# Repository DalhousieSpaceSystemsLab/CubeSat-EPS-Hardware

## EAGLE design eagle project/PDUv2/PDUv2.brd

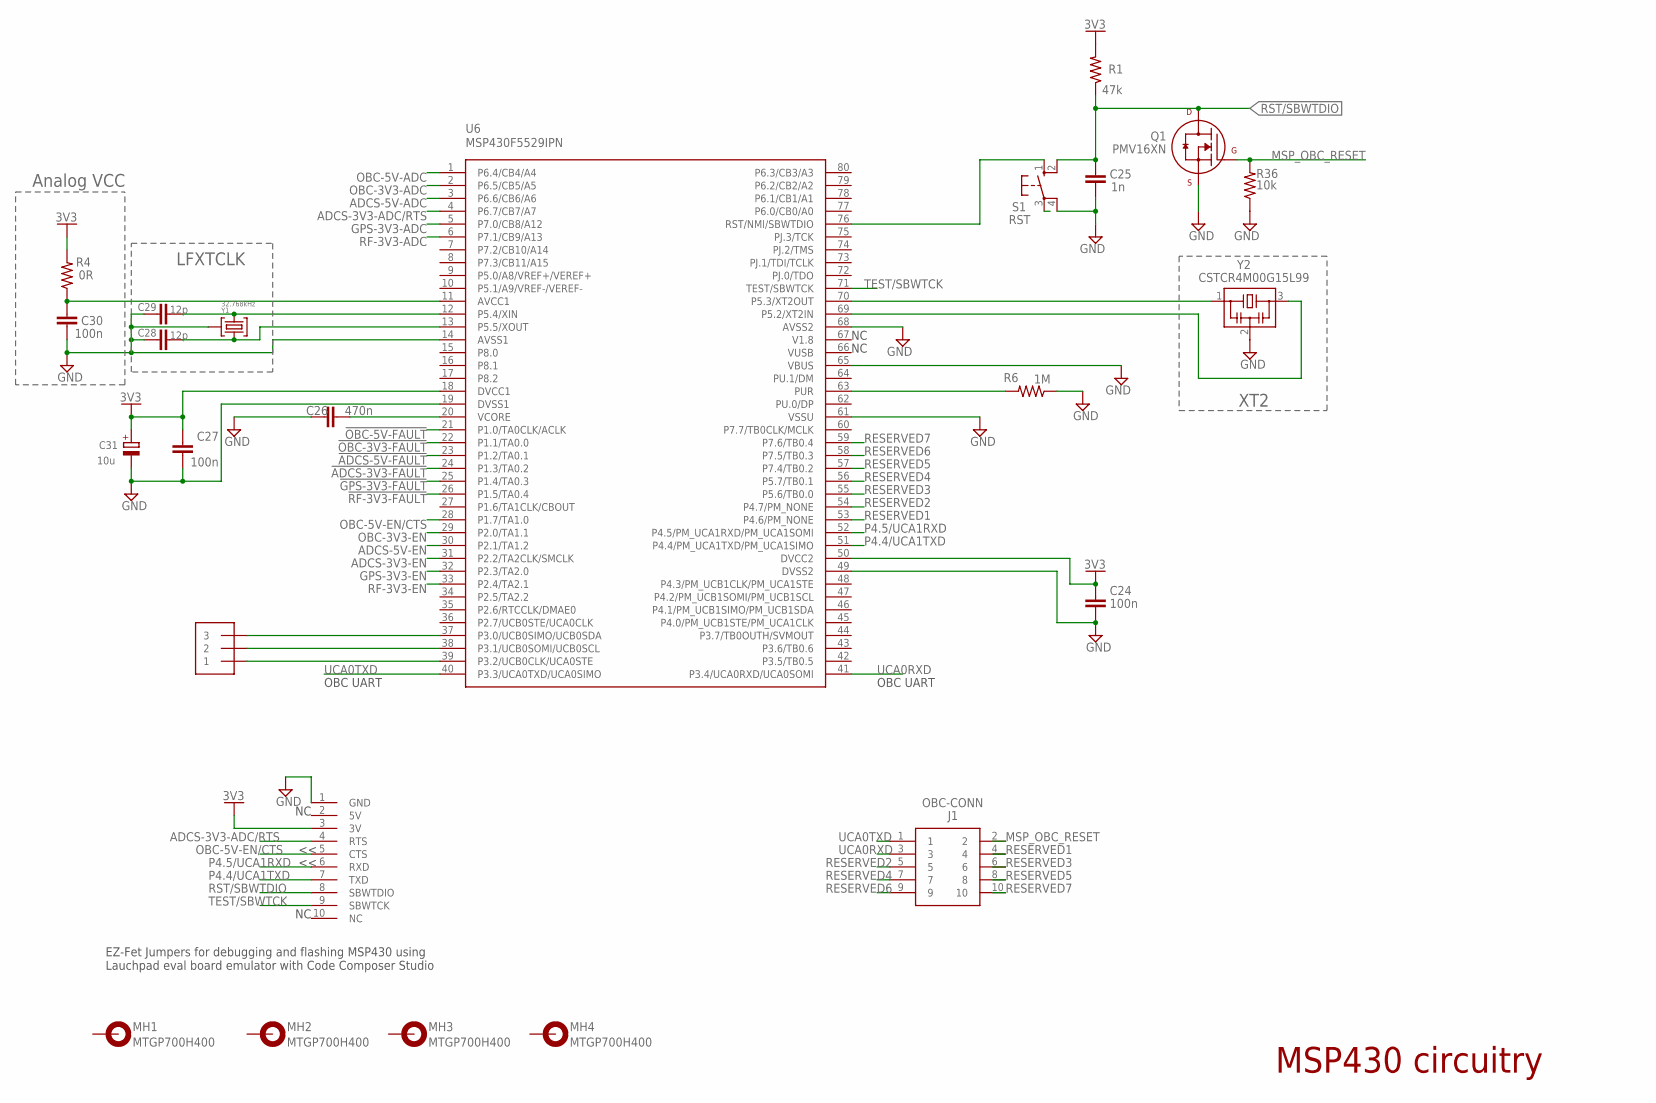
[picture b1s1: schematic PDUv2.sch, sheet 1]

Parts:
C24, C27, C30: 100n; C0402
C25: 1n; C0402
C26: 470n; C0402
C28, C29: 12p; C0402
C31: 10u; A/3216-18R
J1: OBC-CONN
J5: HDR_10_EZFET_DEBUGGER; HDRV10W66P254_10X1_2540X254H858
MH1, MH2, MH3, MH4: MTGP700H400
Q1: PMV16XN; SOT23-3P95_230X110L20X43N_PMV16XN
R1: 47k; R0402
R4: 0R; R0402
R6: 1M; R0603
R36: 10k; R0603
S1: RST; B3F-10XX
U6: MSP430F5529IPN; QFP80P50_1400X1400X160L60X22N
U$23: GRPB031VWTC-RC
Y1: 32.768kHz; MS3V-T1R
Y2: CSTCR4M00G15L99; MURATA-FILTER_CSTCR

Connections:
3V3: C27.2, C31.+, J5.3 (3V), R1.2, R4.2, U6.18 (DVCC1); also elsewhere on the board
!ADCS-3V3-FAULT: U6.24 (P1.3/TA0.2); also elsewhere on the board
!ADCS-5V-FAULT: U6.23 (P1.2/TA0.1); also elsewhere on the board
!GPS-3V3-FAULT: U6.25 (P1.4/TA0.3); also elsewhere on the board
!OBC-3V3-FAULT: U6.22 (P1.1/TA0.0); also elsewhere on the board
!OBC-5V-FAULT: U6.21 (P1.0/TA0CLK/ACLK); also elsewhere on the board
!RF-3V3-FAULT: U6.26 (P1.5/TA0.4); also elsewhere on the board
ADCS-3V3-ADC/RTS: J5.4 (RTS), U6.4 (P6.7/CB7/A7); also elsewhere on the board
ADCS-3V3-EN: U6.31 (P2.2/TA2CLK/SMCLK); also elsewhere on the board
ADCS-5V-ADC: U6.3 (P6.6/CB6/A6); also elsewhere on the board
ADCS-5V-EN: U6.30 (P2.1/TA1.2); also elsewhere on the board
AVCC1: C30.1, R4.1, U6.11 (AVCC1)
GND: C24.2, C25.2, C26.1, C27.1, C28.1, C29.1, C30.2, C31.-, J5.1 (GND), Q1.2 (S), R6.1, R36.1, S1.4 (P1), U6.14 (AVSS1), U6.19 (DVSS1), U6.49 (DVSS2), U6.61 (VSSU), U6.65 (VBUS), U6.68 (AVSS2), Y1.P3 (GND), Y2.2; also elsewhere on the board
GPS-3V3-ADC: U6.5 (P7.0/CB8/A12); also elsewhere on the board
GPS-3V3-EN: U6.32 (P2.3/TA2.0); also elsewhere on the board
MSP_OBC_RESET: J1.2, Q1.1 (G), R36.2
unnamed: C24.1, U6.50 (DVCC2)
unnamed: S1.1 (S), U6.76 (RST/NMI/SBWTDIO)
OBC-3V3-ADC: U6.2 (P6.5/CB5/A5); also elsewhere on the board
OBC-3V3-EN: U6.29 (P2.0/TA1.1); also elsewhere on the board
OBC-5V-ADC: U6.1 (P6.4/CB4/A4); also elsewhere on the board
OBC-5V-EN/CTS: J5.5 (CTS), U6.28 (P1.7/TA1.0); also elsewhere on the board
P4.4/UCA1TXD: J5.7 (TXD), U6.51 (P4.4/PM_UCA1TXD/PM_UCA1SIMO)
P4.5/UCA1RXD: J5.6 (RXD), U6.52 (P4.5/PM_UCA1RXD/PM_UCA1SOMI)
P5.2/XT2IN1: U6.69 (P5.2/XT2IN), Y2.3
P5.3/XT2OUT1: U6.70 (P5.3/XT2OUT), Y2.1
P5.4/XIN1: C29.2, U6.12 (P5.4/XIN), Y1.P1 (1)
P5.5/XOUT1: C28.2, U6.13 (P5.5/XOUT), Y1.P2 (2)
RESERVED1: J1.4, U6.53 (P4.6/PM_NONE)
RESERVED2: J1.5, U6.54 (P4.7/PM_NONE)
RESERVED3: J1.6, U6.55 (P5.6/TB0.0)
RESERVED4: J1.7, U6.56 (P5.7/TB0.1)
RESERVED5: J1.8, U6.57 (P7.4/TB0.2)
RESERVED6: J1.9, U6.58 (P7.5/TB0.3)
RESERVED7: J1.10, U6.59 (P7.6/TB0.4)
RF-3V3-ADC: U6.6 (P7.1/CB9/A13); also elsewhere on the board
RF-3V3-EN: U6.33 (P2.4/TA2.1); also elsewhere on the board
RST/SBWTDIO: C25.1, J5.8 (SBWTDIO), Q1.3 (D), R1.1, S1.2 (S1)
TARGET_PUR: R6.2, U6.63 (PUR)
TEST/SBWTCK: J5.9 (SBWTCK), U6.71 (TEST/SBWTCK)
UCA0RXD: J1.3, U6.41 (P3.4/UCA0RXD/UCA0SOMI)
UCA0TXD: J1.1, U6.40 (P3.3/UCA0TXD/UCA0SIMO)
UCB0CLK: U6.39 (P3.2/UCB0CLK/UCA0STE), U$23.1
UCB0SCL: U6.38 (P3.1/UCB0SOMI/UCB0SCL), U$23.2
UCB0SDA: U6.37 (P3.0/UCB0SIMO/UCB0SDA), U$23.3
VCORE1: C26.2, U6.20 (VCORE)

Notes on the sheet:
LFXTCLK
XT2
Analog VCC
OBC UART
EZ-Fet Jumpers for debugging and flashing MSP430 using Lauchpad eval board emulator with Code Composer Studio
MSP430 circuitry

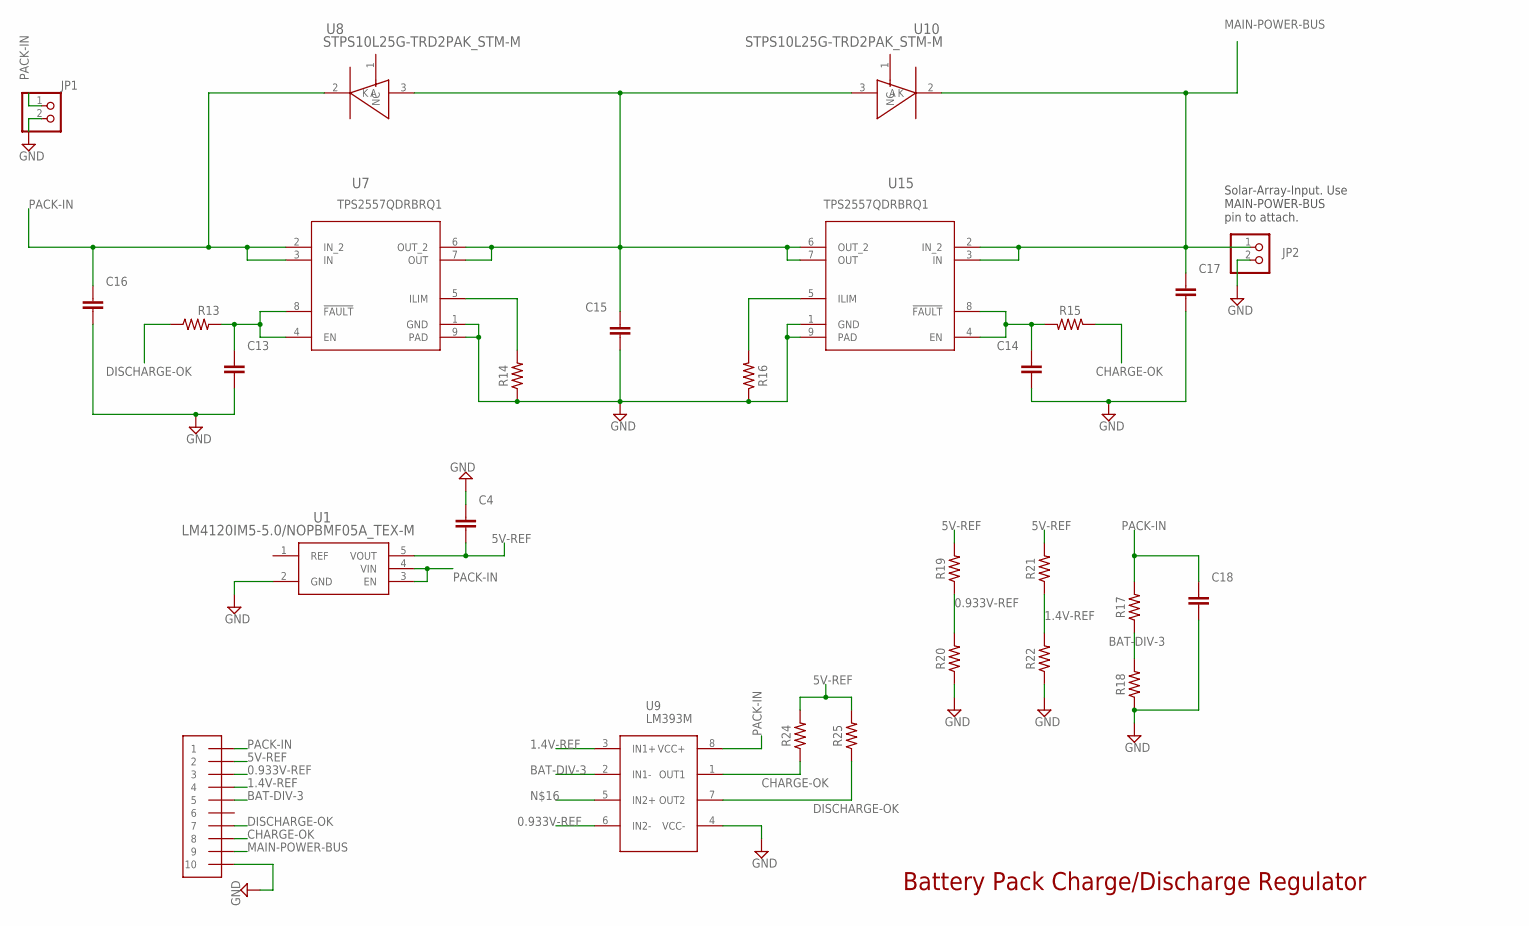
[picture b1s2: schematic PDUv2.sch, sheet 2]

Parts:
C4: 0.022u; CAPC1608X85
C13, C14: 0.22u; CAPC1608X85
C15: 10u; CAPC1608X85
C16, C17: 0.1u; CAPC1608X85
C18: 1u; CAPC1608X85
JP1, JP2: PINHD-1X2; 1X02
R13, R15: 100k; RESC1608X60
R14, R16: 20k; RESC1608X60
R17: 340k; RESC1608X60
R18: 169k; RESC1608X60
R19: 1.62M; RESC1608X60
R20: 374k; RESC1608X60
R21: 1.43M; RESC1608X60
R22: 562k; RESC1608X60
R24, R25: 332k; RESC1608X60
U1: LM4120IM5-5.0/NOPBMF05A_TEX-M; MF05A_TEX-M
U7, U15: Value; DRB0008B
U8, U10: STPS10L25G-TRD2PAK_STM-M; D2PAK_STM-M
U9: LM393M; M08A-M
U$20: GRPB052VWQS-RC

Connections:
0.933V-REF: R19.1, R20.2, U9.6 (IN2-), U$20.3
1.4V-REF: R21.1, R22.2, U9.3 (IN1+), U$20.4
5V-REF: C4.2, R19.2, R21.2, R24.2, R25.2, U1.5 (VOUT), U$20.2
BAT-DIV-3: R17.1, R18.2, U9.2 (IN1-), U$20.5
CHARGE-OK: R15.1, R24.1, U9.1 (OUT1), U$20.8
DISCHARGE-OK: R13.1, R25.1, U9.7 (OUT2), U$20.7
GND: C4.1, C13.2, C14.2, C15.2, C16.2, C17.2, C18.2, JP1.2, JP2.2, R14.1, R16.1, R18.1, R20.1, R22.1, U1.2 (GND), U7.1 (GND), U7.9 (PAD), U9.4 (VCC-), U15.1 (GND), U15.9 (PAD), U$20.10; also elsewhere on the board
MAIN-POWER-BUS: C17.1, JP2.1, U10.2 (K), U15.2 (IN_2), U15.3 (IN), U$20.9; also elsewhere on the board
unnamed: C15.1, U7.6 (OUT_2), U7.7 (OUT), U8.3 (A), U10.3 (A), U15.6 (OUT_2), U15.7 (OUT)
unnamed: C13.1, R13.2, U7.4 (EN), U7.8 (!FAULT)
unnamed: R14.2, U7.5 (ILIM)
unnamed: C14.1, R15.2, U15.4 (EN), U15.8 (!FAULT)
unnamed: R16.2, U15.5 (ILIM)
PACK-IN: C16.1, C18.1, JP1.1, R17.2, U1.3 (EN), U1.4 (VIN), U7.2 (IN_2), U7.3 (IN), U8.2 (K), U9.8 (VCC+), U$20.1

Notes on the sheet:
Solar-Array-Input. Use MAIN-POWER-BUS pin to attach.
Battery Pack Charge/Discharge Regulator

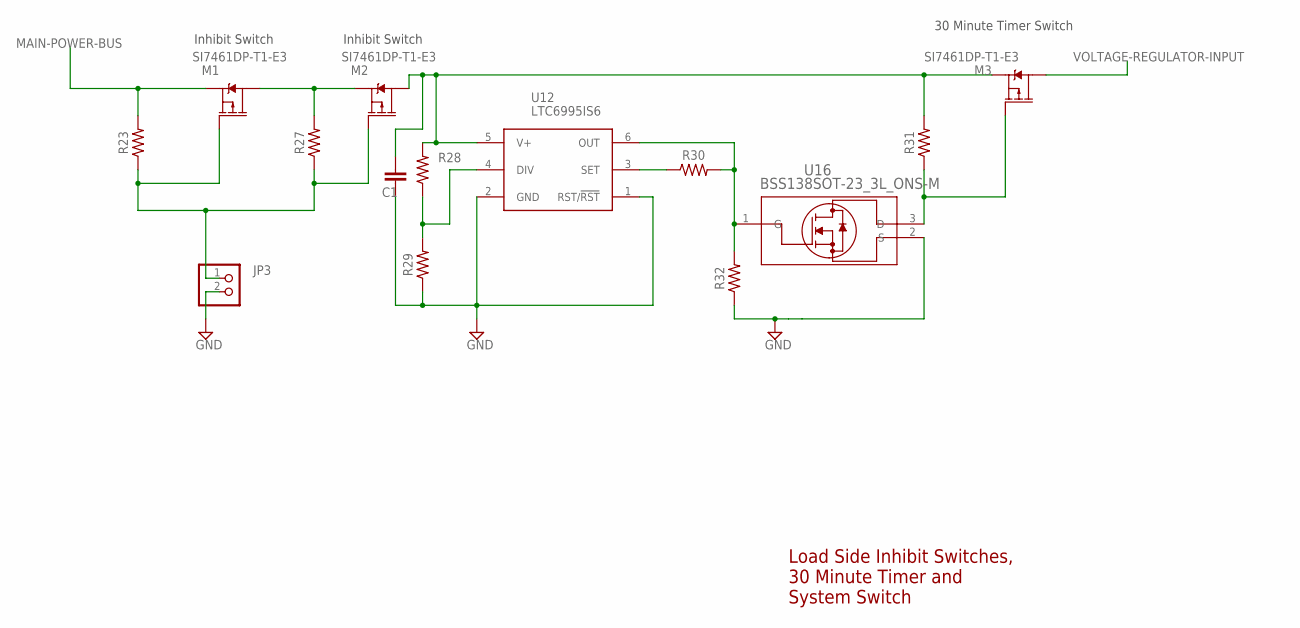
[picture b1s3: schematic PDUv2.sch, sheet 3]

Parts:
C1: 0.1u; CAPC1608X85
JP3: PINHD-1X2; 1X02
M1, M2, M3: SI7461DP-T1-E3; MOSFET_65DP-T1-E3_VIS
R23, R27, R31: 499k; RESC1608X60
R28: 1Meg; RESC1608X60
R29: 392k; RESC1608X60
R30: 715k; RESC1608X60
R32: 100k; RESC1608X60
U12: LTC6995IS6; TSOT-23_S6_LIT
U16: BSS138SOT-23_3L_ONS-M; SOT-23_3L_ONS-M

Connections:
GND: C1.2, JP3.2, R29.1, R32.1, U12.1 (RST/!RST), U12.2 (GND), U16.2 (S); also elsewhere on the board
MAIN-POWER-BUS: M1.1 (S), M1.2 (S), M1.3 (S), R23.2; also elsewhere on the board
unnamed: M3.4 (G), R31.1, U16.3 (D)
unnamed: JP3.1, M1.4 (G), M2.4 (G), R23.1, R27.1
unnamed: C1.1, M2.5 (D), M2.6 (D), M2.7 (D), M2.8 (D), M3.1 (S), M3.2 (S), M3.3 (S), R28.2, R31.2, U12.5 (V+)
unnamed: M1.5 (D), M1.6 (D), M1.7 (D), M1.8 (D), M2.1 (S), M2.2 (S), M2.3 (S), R27.2
unnamed: R28.1, R29.2, U12.4 (DIV)
unnamed: R30.1, U12.3 (SET)
unnamed: R30.2, R32.2, U12.6 (OUT), U16.1 (G)
VOLTAGE-REGULATOR-INPUT: M3.5 (D), M3.6 (D), M3.7 (D), M3.8 (D); also elsewhere on the board

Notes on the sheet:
Inhibit Switch
30 Minute Timer Switch
Load Side Inhibit Switches, 30 Minute Timer and System Switch

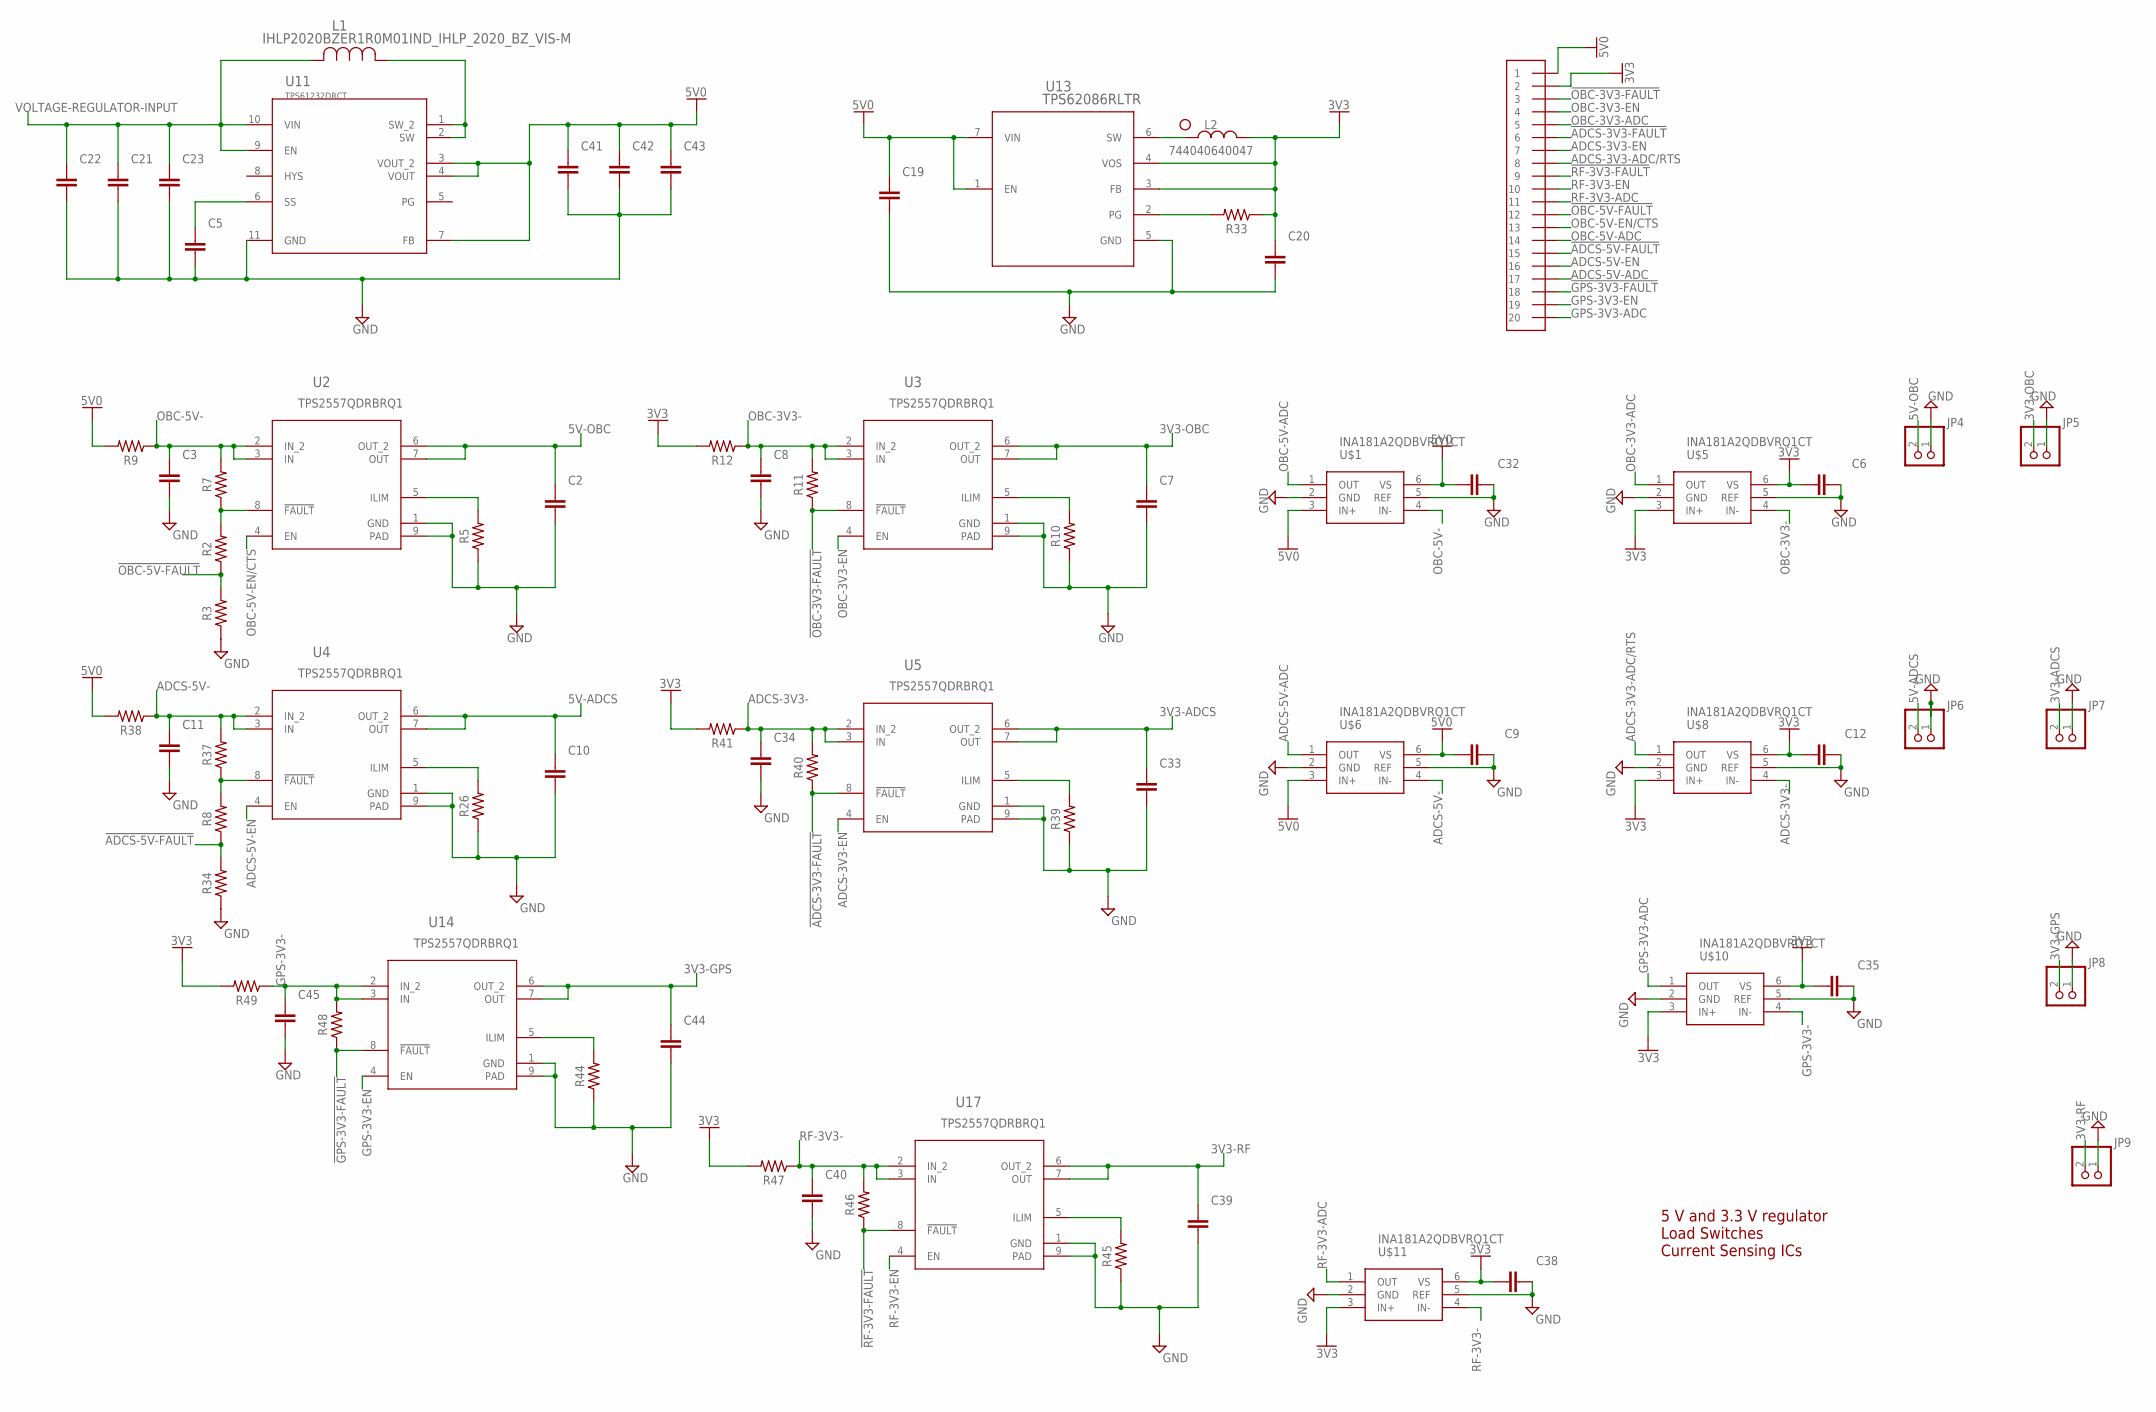
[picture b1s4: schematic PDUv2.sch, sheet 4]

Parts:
C2, C7, C10, C33, C39, C44: 47u; CAPC1608X85
C3, C6, C8, C9, C11, C12, C32, C34, C35, C38, C40, C45: 0.1u; CAPC1608X85
C5: 15n; CAPC1608X85
C19, C20, C21, C22, C23, C41, C42, C43: 10u; CAPC1608X85
JP4, JP5, JP6, JP7, JP8, JP9: PINHD-1X2; 1X02
L1: IHLP2020BZER1R0M01IND_IHLP_2020_BZ_VIS-M; IND_IHLP_2020_BZ_VIS-M
L2: 744040640047
R2, R7, R8, R11, R37, R40, R46, R48: 100k; RESC1608X60
R3, R34: 196k; RESC1608X60
R5, R10, R26, R39, R44, R45: 54.9k; RESC1608X60
R9, R12, R38, R41, R47, R49: 40m; RESC1608X60
R33: 1M; RESC1608X60
U2, U3, U4, U5, U14, U17: Value; DRB0008B
U11: TPS61232DRCT; DRC0010G
U13: TPS62086RLTR; RLT0007A
U$1, U$5, U$6, U$8, U$10, U$11: INA181A2QDBVRQ1CT; TSOT-23_S6_LIT-M
U$21: GRPB102VWQS-RC

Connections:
3V3: C6.1, C12.1, C20.1, C35.1, C38.1, L2.2, R12.2, R33.1, R41.2, R47.2, R49.2, U13.3 (FB), U13.4 (VOS), U$5.6 (VS), U$8.6 (VS), U$10.6 (VS), U$11.6 (VS), U$21.2; also elsewhere on the board
3V3-ADCS: C33.1, JP7.2, U5.6 (OUT_2), U5.7 (OUT)
3V3-GPS: C44.1, JP8.2, U14.6 (OUT_2), U14.7 (OUT)
3V3-OBC: C7.1, JP5.2, U3.6 (OUT_2), U3.7 (OUT)
3V3-RF: C39.1, JP9.2, U17.6 (OUT_2), U17.7 (OUT)
5V0: C19.1, C41.1, C42.1, C43.1, R9.2, R38.2, U11.3 (VOUT_2), U11.4 (VOUT), U11.7 (FB), U13.1 (EN), U13.7 (VIN), U$1.3 (IN+), U$6.3 (IN+), U$21.1
5V-ADCS: C10.1, JP6.2, U4.6 (OUT_2), U4.7 (OUT)
5V-OBC: C2.1, JP4.2, U2.6 (OUT_2), U2.7 (OUT)
!ADCS-3V3-FAULT: R40.1, U5.8 (!FAULT), U$21.6; also elsewhere on the board
!ADCS-5V-FAULT: R8.1, R34.2, U$21.15; also elsewhere on the board
!GPS-3V3-FAULT: R48.1, U14.8 (!FAULT), U$21.18; also elsewhere on the board
!OBC-3V3-FAULT: R11.1, U3.8 (!FAULT), U$21.3; also elsewhere on the board
!OBC-5V-FAULT: R2.1, R3.2, U$21.12; also elsewhere on the board
!RF-3V3-FAULT: R46.1, U17.8 (!FAULT), U$21.9; also elsewhere on the board
ADCS-3V3-: C34.1, R40.2, R41.1, U5.2 (IN_2), U5.3 (IN), U$8.4 (IN-)
ADCS-3V3-ADC/RTS: U$8.1 (OUT), U$21.8; also elsewhere on the board
ADCS-3V3-EN: U5.4 (EN), U$21.7; also elsewhere on the board
ADCS-5V-: C11.1, R37.2, R38.1, U4.2 (IN_2), U4.3 (IN), U$6.4 (IN-)
ADCS-5V-ADC: U$6.1 (OUT), U$21.17; also elsewhere on the board
ADCS-5V-EN: U4.4 (EN), U$21.16; also elsewhere on the board
GND: C2.2, C3.2, C5.2, C6.2, C7.2, C8.2, C9.2, C10.2, C11.2, C12.2, C19.2, C20.2, C21.2, C22.2, C23.2, C32.2, C33.2, C34.2, C35.2, C38.2, C39.2, C40.2, C41.2, C42.2, C43.2, C44.2, C45.2, JP4.1, JP5.1, JP6.1, JP7.1, JP8.1, JP9.1, R3.1, R5.1, R10.1, R26.1, R34.1, R39.1, R44.1, R45.1, U2.1 (GND), U2.9 (PAD), U3.1 (GND), U3.9 (PAD), U4.1 (GND), U4.9 (PAD), U5.1 (GND), U5.9 (PAD), U11.11 (GND), U13.5 (GND), U14.1 (GND), U14.9 (PAD), U17.1 (GND), U17.9 (PAD), U$1.5 (REF), U$5.5 (REF), U$6.5 (REF), U$8.5 (REF), U$10.5 (REF), U$11.5 (REF); also elsewhere on the board
GPS-3V3-: C45.1, R48.2, R49.1, U14.2 (IN_2), U14.3 (IN), U$10.4 (IN-)
GPS-3V3-ADC: U$10.1 (OUT), U$21.20; also elsewhere on the board
GPS-3V3-EN: U14.4 (EN), U$21.19; also elsewhere on the board
unnamed: R5.2, U2.5 (ILIM)
unnamed: R10.2, U3.5 (ILIM)
unnamed: R26.2, U4.5 (ILIM)
unnamed: R39.2, U5.5 (ILIM)
unnamed: R45.2, U17.5 (ILIM)
unnamed: R2.2, R7.1, U2.8 (!FAULT)
unnamed: R8.2, R37.1, U4.8 (!FAULT)
unnamed: L1.1, U11.1 (SW_2), U11.2 (SW)
unnamed: C5.1, U11.6 (SS)
unnamed: R44.2, U14.5 (ILIM)
unnamed: C32.1, U$1.6 (VS)
unnamed: L2.1 (DOT), U13.6 (SW)
unnamed: R33.2, U13.2 (PG)
unnamed: C9.1, U$6.6 (VS)
OBC-3V3-: C8.1, R11.2, R12.1, U3.2 (IN_2), U3.3 (IN), U$5.4 (IN-)
OBC-3V3-ADC: U$5.1 (OUT), U$21.5; also elsewhere on the board
OBC-3V3-EN: U3.4 (EN), U$21.4; also elsewhere on the board
OBC-5V-: C3.1, R7.2, R9.1, U2.2 (IN_2), U2.3 (IN), U$1.4 (IN-)
OBC-5V-ADC: U$1.1 (OUT), U$21.14; also elsewhere on the board
OBC-5V-EN/CTS: U2.4 (EN), U$21.13; also elsewhere on the board
RF-3V3-: C40.1, R46.2, R47.1, U17.2 (IN_2), U17.3 (IN), U$11.4 (IN-)
RF-3V3-ADC: U$11.1 (OUT), U$21.11; also elsewhere on the board
RF-3V3-EN: U17.4 (EN), U$21.10; also elsewhere on the board
VOLTAGE-REGULATOR-INPUT: C21.1, C22.1, C23.1, L1.2, U11.9 (EN), U11.10 (VIN); also elsewhere on the board

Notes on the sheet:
5 V and 3.3 V regulator Load Switches Current Sensing ICs

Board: 2 copper layers, 139 parts (0 on the bottom side), 94 nets, no tracks yet.

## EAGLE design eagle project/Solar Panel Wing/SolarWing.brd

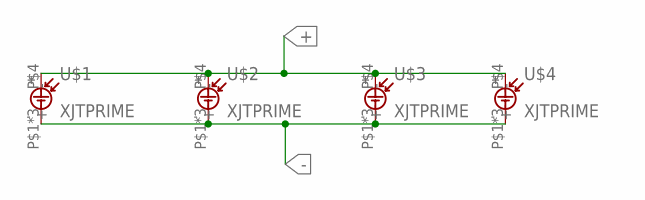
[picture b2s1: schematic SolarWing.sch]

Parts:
U$1, U$2, U$3, U$4: XJTPRIME

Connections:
+: U$1.P$4 (+), U$2.P$4 (+), U$3.P$4 (+), U$4.P$4 (+)
-: U$1.P$1 (-), U$1.P$2 (-), U$1.P$3 (-), U$2.P$1 (-), U$2.P$2 (-), U$2.P$3 (-), U$3.P$1 (-), U$3.P$2 (-), U$3.P$3 (-), U$4.P$1 (-), U$4.P$2 (-), U$4.P$3 (-)

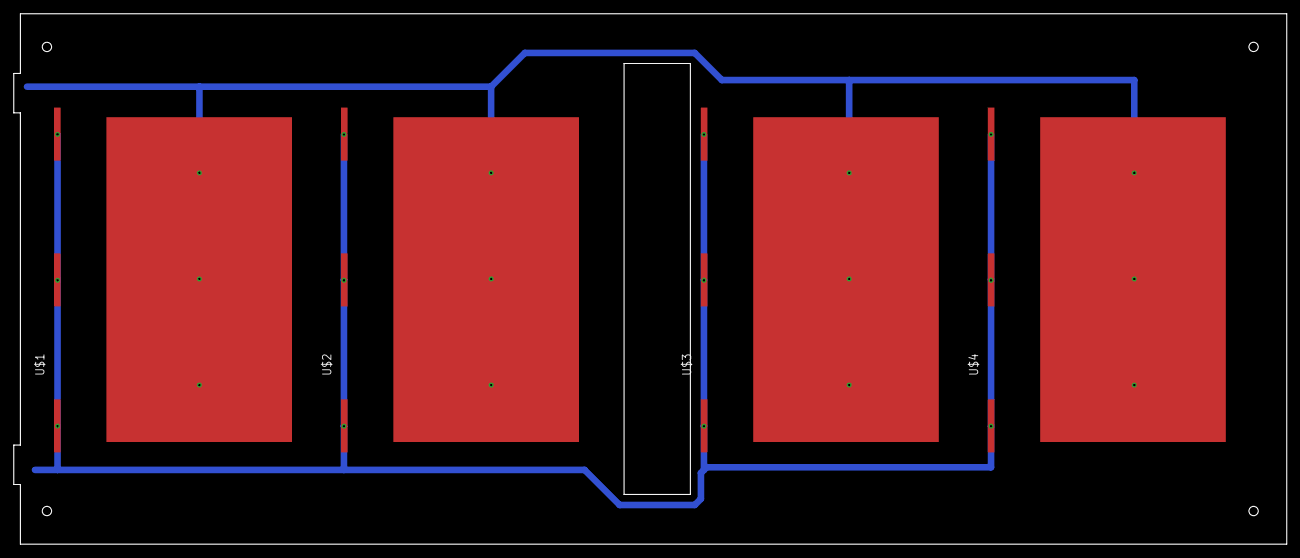
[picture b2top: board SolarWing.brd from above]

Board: 2 copper layers, 192.0 x 80.0 mm, 4 parts (0 on the bottom side), 2 nets.

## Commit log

2021-07-01 moved over to organization loris organization
2021-07-28 added wall
2021-08-02 added 2nd prog
2021-08-12 removed backup files
2021-08-12 added .gitignore file to ignore backup versions

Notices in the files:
parts and their libraries:
COPYRIGHT: Copyright (C) 2018 Accelerated Designs. All rights reserved
